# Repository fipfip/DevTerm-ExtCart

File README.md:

# DevTerm-ExtCart

An extension board for the DevTerm, with Commodore64-style 44pin cartridge.

## Design desiderata

Pin assignment:
- Maximum compatibility and function alignment.
- Strong coupling of differential pairs.
- Avoid damage.
All power pins are mirror safe.
Expansion port requirement:
- Pin 21 MUST connect to Pin 23.
- Pin 24 MUST be NC
ROUTE_EN disconnects all routed pins when cartridge is:
- Disconnected
- Inserted the wrong direction
Resource overview:
- 8x internal GPIOs
- 8x external GPIOs
- MIPI-CSI
- 3x USB 2.0
- 1x SPI
- 1x I2C
- 1x UART (Debug)
Resource management pins:
- IO36 for power management
- IO43 for cartridge detection

## PCB Physical specifications

- EXT board:
  - size: 89mm (height) x 101mm (width)
  - thickness: 1mm (source: https://www.ampltd.com/minipcie/)
- Carts:
  - size: 61mm (max height inside DevTerm) x 58.42mm (width)
  - thickness: 1.6mm (source: https://dirtypcbs.com/store/designer/details/12317/1036/cartridge-board-for-commodore-64)

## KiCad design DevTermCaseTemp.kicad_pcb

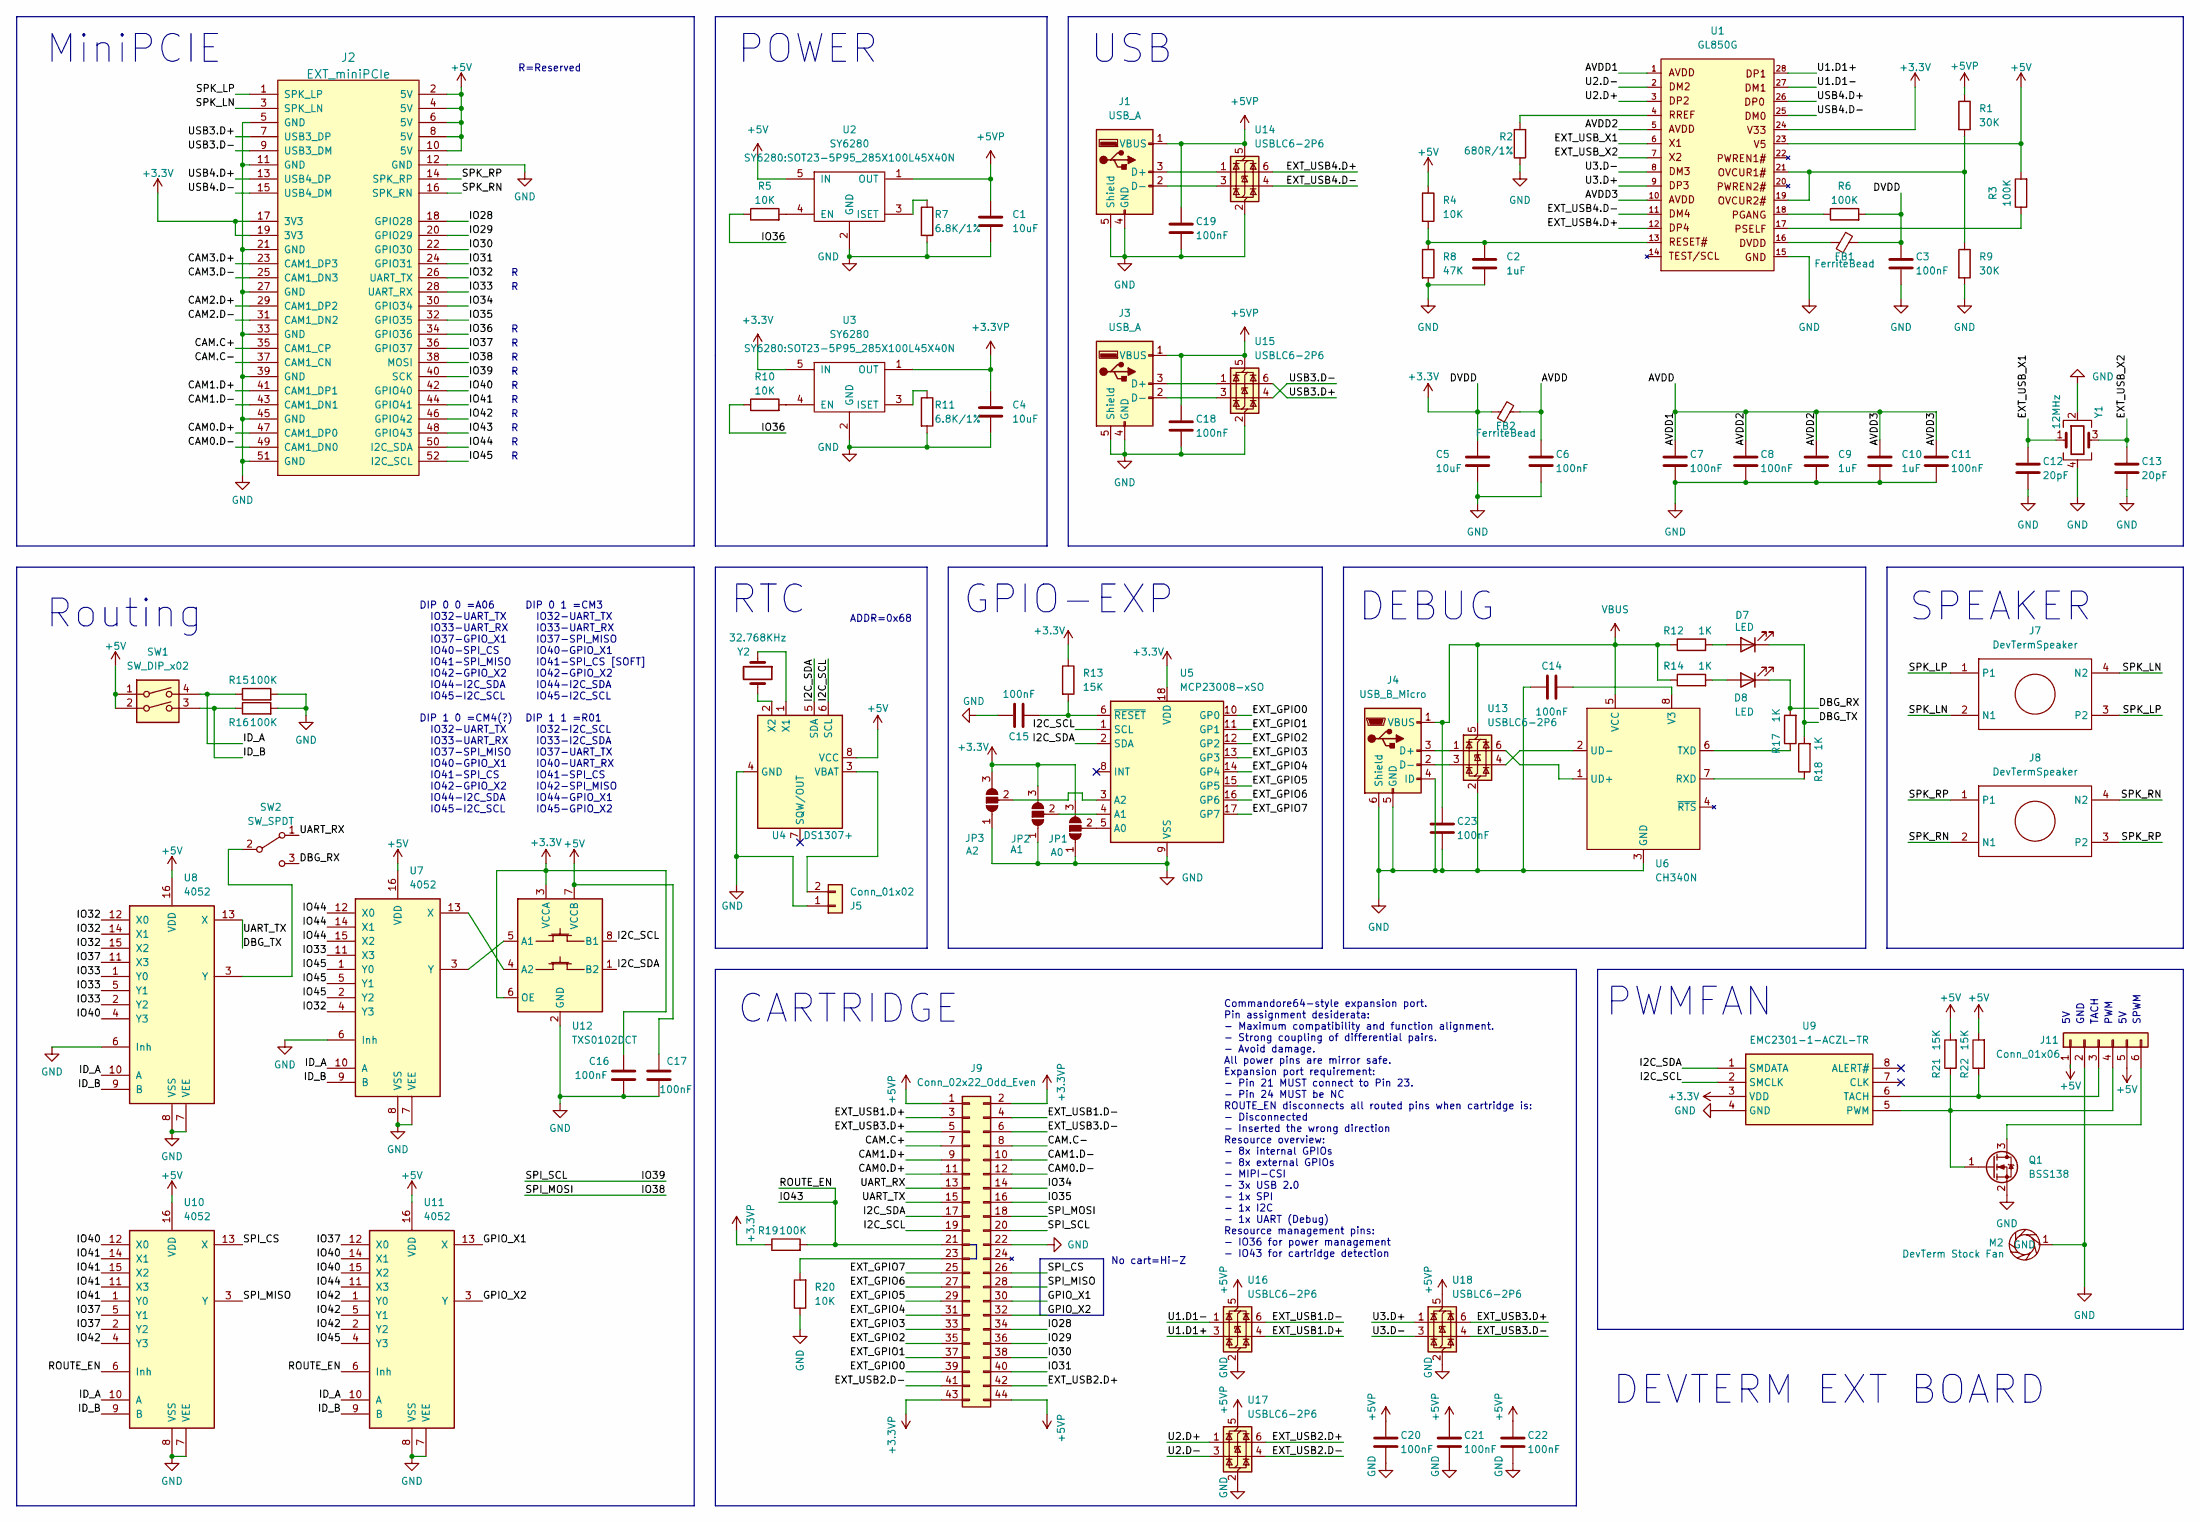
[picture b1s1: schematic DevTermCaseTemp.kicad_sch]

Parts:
C1, C4, C5: 10uF; C_0805_2012Metric
C2, C9, C10: 1uF; C_0805_2012Metric
C3, C6, C7, C8, C11, C14, C15, C16, C17, C18, C19, C20, C21, C22, C23: 100nF; C_0805_2012Metric
C12, C13: 20pF; C_0805_2012Metric
D7, D8: LED; LED_0603_1608Metric
FB1, FB2: FerriteBead; C_0805_2012Metric
J1, J3: USB_A; USB_A_PCBCUT
J2: EXT_miniPCIe; mini-PCIe
J4: USB_B_Micro; USB_Micro-B_Amphenol_10118194_Horizontal
J5: Conn_01x02; Molex_PicoBlade_53048-0210_1x02_P1.25mm_Horizontal
J7, J8: DevTermSpeaker; DevTerm-Speaker
J9: Conn_02x22_Odd_Even; C64-Cart-Socket-Horizontal
J11: Conn_01x06; PinHeader_1x06_P2.00mm_Horizontal
JP1: A0; SolderJumper-3_P1.3mm_Open_Pad1.0x1.5mm
JP2: A1; SolderJumper-3_P1.3mm_Open_Pad1.0x1.5mm
JP3: A2; SolderJumper-3_P1.3mm_Open_Pad1.0x1.5mm
M2: DevTerm Stock Fan; DevTerm-Stock-Fan
Q1: BSS138; SOT-23
R1, R9: 30K; R_0805_2012Metric
R2: 680R/1%; R_0805_2012Metric
R3, R6, R15, R16, R19: 100K; R_0805_2012Metric
R4, R5, R10, R20: 10K; R_0805_2012Metric
R7, R11: 6.8K/1%; R_0805_2012Metric
R8: 47K; R_0805_2012Metric
R12, R14, R17, R18: 1K; R_0805_2012Metric
R13, R21, R22: 15K; R_0805_2012Metric
SW1: SW_DIP_x02; SW_DIP_SPSTx02_Slide_6.7x6.64mm_W8.61mm_P2.54mm_LowProfile
SW2: SW_SPDT; SW_CuK_OS102011MA1QN1_SPDT_Angled
U1: GL850G; SSOP28
U2, U3: SY6280; SOT23-5P95_285X100L45X40N
U4: DS1307+; SOIC-8
U5: MCP23008-xSO; SOIC-18W_7.5x11.6mm_P1.27mm
U6: CH340N; SOP-8_3.9x4.9mm_P1.27mm
U7, U8, U10, U11: 4052; SOIC-16_3.9x9.9mm_P1.27mm
U9: EMC2301-1-ACZL-TR; SOP65P490X110-8N; Mouser Part Number 886-EMC2301-1-ACZLTR
U12: TXS0102DCT; MSOP-8_3x3mm_P0.65mm
U13, U14, U15, U16, U17, U18: USBLC6-2P6; SOT-666
Y1: 12MHz; Crystal_SMD_3225-4Pin_3.2x2.5mm_HandSoldering
Y2: 32.768KHz; Crystal_DS26_D2.0mm_L6.0mm_Horizontal

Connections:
+3.3V: C3.1, C5.1, C16.1, FB1.2, FB2.1, J2.17 (3V3), J2.19 (3V3), JP1.3 (B), JP2.3 (B), JP3.3 (B), R6.2, R13.1, U1.24, U3.5 (IN), U5.18 (VDD), U9.3 (VDD), U12.3 (VCCA), U12.6 (OE)
+3.3VP: C4.1, J9.2, J9.43, R19.1, U3.1 (OUT)
+5V: C17.1, J2.2 (5V), J2.4 (5V), J2.6 (5V), J2.8 (5V), J2.10 (5V), J11.1, J11.5, R3.2, R4.1, R21.2, R22.2, SW1.1, SW1.2, U1.23, U2.5 (IN), U4.8 (VCC), U7.16 (VDD), U8.16 (VDD), U10.16 (VDD), U11.16 (VDD), U12.7 (VCCB)
+5VP: C1.1, C18.1, C19.1, C20.1, C21.1, C22.1, J1.1 (VBUS), J3.1 (VBUS), J9.1, J9.44, R1.1, U2.1 (OUT), U14.5 (VBUS), U15.5 (VBUS), U16.5 (VBUS), U17.5 (VBUS), U18.5 (VBUS)
/AVDD: C6.1, C7.1, C8.1, C9.1, C10.1, C11.1, FB2.2, U1.1, U1.5, U1.10
/CAM0.D+: J2.47 (CAM1_DP0), J9.11
/CAM0.D-: J2.49 (CAM1_DN0), J9.12
/CAM1.D+: J2.41 (CAM1_DP1), J9.9
/CAM1.D-: J2.43 (CAM1_DN1), J9.10
/CAM2.D+: J2.29 (CAM1_DP2)
/CAM2.D-: J2.31 (CAM1_DN2)
/CAM3.D+: J2.23 (CAM1_DP3)
/CAM3.D-: J2.25 (CAM1_DN3)
/CAM.C+: J2.35 (CAM1_CP), J9.7
/CAM.C-: J2.37 (CAM1_CN), J9.8
/DBG_RX: D8.1 (K), R17.2, SW2.3 (C)
/DBG_TX: D7.1 (K), J9.15, R18.2, U8.13 (X)
/EXT_GPIO0: J9.39, U5.10 (GP0)
/EXT_GPIO1: J9.37, U5.11 (GP1)
/EXT_GPIO2: J9.35, U5.12 (GP2)
/EXT_GPIO3: J9.33, U5.13 (GP3)
/EXT_GPIO4: J9.31, U5.14 (GP4)
/EXT_GPIO5: J9.29, U5.15 (GP5)
/EXT_GPIO6: J9.27, U5.16 (GP6)
/EXT_GPIO7: J9.25, U5.17 (GP7)
/EXT_USB1.D+: J9.3, U16.4 (I/O2)
/EXT_USB1.D-: J9.4, U16.6 (I/O1)
/EXT_USB2.D+: J9.42, U17.6 (I/O1)
/EXT_USB2.D-: J9.41, U17.4 (I/O2)
/EXT_USB3.D+: J9.5, U18.6 (I/O1)
/EXT_USB3.D-: J9.6, U18.4 (I/O2)
/EXT_USB4.D+: U1.12, U14.6 (I/O1)
/EXT_USB4.D-: U1.11, U14.4 (I/O2)
/EXT_USB_X1: C12.1, U1.6, Y1.1
/EXT_USB_X2: C13.1, U1.7, Y1.3
/GPIO_X1: J9.30, U11.13 (X)
/GPIO_X2: J9.32, U11.3 (Y)
/I2C_SCL: J9.19, U4.6 (SCL), U5.1 (SCL), U9.2 (SMCLK), U12.8 (B1)
/I2C_SDA: J9.17, U4.5 (SDA), U5.2 (SDA), U9.1 (SMDATA), U12.1 (B2)
/ID_A: R15.1, SW1.4, U7.10 (A), U8.10 (A), U10.10 (A), U11.10 (A)
/ID_B: R16.1, SW1.3, U7.9 (B), U8.9 (B), U10.9 (B), U11.9 (B)
/IO28: J2.18 (GPIO28), J9.34
/IO29: J2.20 (GPIO29), J9.36
/IO30: J2.22 (GPIO30), J9.38
/IO31: J2.24 (GPIO31), J9.40
/IO32: J2.26 (UART_TX), U7.4 (Y3), U8.12 (X0), U8.14 (X1), U8.15 (X2)
/IO33: J2.28 (UART_RX), U7.11 (X3), U8.1 (Y0), U8.2 (Y2), U8.5 (Y1)
/IO34: J2.30 (GPIO34), J9.14
/IO35: J2.32 (GPIO35), J9.16
/IO36: J2.34 (GPIO36), R5.1, R10.1
/IO37: J2.36 (GPIO37), U8.11 (X3), U10.2 (Y2), U10.5 (Y1), U11.12 (X0)
/IO38: J2.38 (MOSI), J9.18
/IO39: J2.40 (SCK), J9.20
/IO40: J2.42 (GPIO40), U8.4 (Y3), U10.12 (X0), U11.14 (X1), U11.15 (X2)
/IO41: J2.44 (GPIO41), U10.1 (Y0), U10.11 (X3), U10.14 (X1), U10.15 (X2)
/IO42: J2.46 (GPIO42), U10.4 (Y3), U11.1 (Y0), U11.2 (Y2), U11.5 (Y1)
/IO43: J2.48 (GPIO43), J9.21, R19.2, U10.6 (Inh), U11.6 (Inh)
/IO44: J2.50 (I2C_SDA), U7.12 (X0), U7.14 (X1), U7.15 (X2), U11.11 (X3)
/IO45: J2.52 (I2C_SCL), U7.1 (Y0), U7.2 (Y2), U7.5 (Y1), U11.4 (Y3)
/SPI_CS: J9.26, U10.13 (X)
/SPI_MISO: J9.28, U10.3 (Y)
/SPK_LN: J2.3 (SPK_LN), J7.2 (N1), J7.4 (N2)
/SPK_LP: J2.1 (SPK_LP), J7.1, J7.3 (P2)
/SPK_RN: J2.16 (SPK_RN), J8.2 (N1), J8.4 (N2)
/SPK_RP: J2.14 (SPK_RP), J8.1, J8.3 (P2)
/U1.D1+: U1.28, U16.3 (I/O2)
/U1.D1-: U1.27, U16.1 (I/O1)
/U2.D+: U1.3, U17.1 (I/O1)
/U2.D-: U1.2, U17.3 (I/O2)
/U3.D+: U1.9, U18.1 (I/O1)
/U3.D-: U1.8, U18.3 (I/O2)
/UART_RX: J9.13, SW2.1 (A)
/USB3.D+: J2.7 (USB3_DP), U15.6 (I/O1)
/USB3.D-: J2.9 (USB3_DM), U15.4 (I/O2)
/USB4.D+: J2.13 (USB4_DP), U1.26
/USB4.D-: J2.15 (USB4_DM), U1.25
GND: C1.2, C2.2, C3.2, C4.2, C5.2, C6.2, C7.2, C8.2, C9.2, C10.2, C11.2, C12.2, C13.2, C14.2, C15.1, C16.2, C17.2, C18.2, C19.2, C20.2, C21.2, C22.2, C23.2, J1.4 (GND), J1.5 (Shield), J2.5 (GND), J2.11 (GND), J2.12 (GND), J2.21 (GND), J2.27 (GND), J2.33 (GND), J2.39 (GND), J2.45 (GND), J2.51 (GND), J3.4 (GND), J3.5 (Shield), J4.4 (ID), J4.5 (GND), J4.6 (Shield), J5.1, J9.22, J11.2, JP1.1 (A), JP2.1 (A), JP3.1 (A), M2.1 (GND), Q1.2 (S), R2.1, R7.2, R8.2, R9.2, R11.2, R15.2, R16.2, R20.1, U1.15, U2.2 (GND), U3.2 (GND), U4.4 (GND), U5.9 (VSS), U6.3 (GND), U7.6 (Inh), U7.7 (VEE), U7.8 (VSS), U8.6 (Inh), U8.7 (VEE), U8.8 (VSS), U9.4 (GND), U10.7 (VEE), U10.8 (VSS), U11.7 (VEE), U11.8 (VSS), U12.2 (GND), U13.2 (GND), U14.2 (GND), U15.2 (GND), U16.2 (GND), U17.2 (GND), U18.2 (GND), Y1.2, Y1.4
unnamed: C2.1, R4.2, R8.1, U1.13
unnamed: D7.2 (A), R12.2
unnamed: D8.2 (A), R14.2
unnamed: FB1.1, U1.16
unnamed: J1.3 (D+), U14.1 (I/O1)
unnamed: J1.2 (D-), U14.3 (I/O2)
unnamed: J3.3 (D+), U15.1 (I/O1)
unnamed: J3.2 (D-), U15.3 (I/O2)
unnamed: J4.3 (D+), U13.1 (I/O1)
unnamed: J4.2 (D-), U13.3 (I/O2)
unnamed: J5.2, U4.3 (VBAT)
unnamed: J9.23, R20.2
unnamed: J11.3, R22.1, U9.6 (TACH)
unnamed: J11.4, Q1.1 (G), R21.1, U9.5 (PWM)
unnamed: J11.6, Q1.3 (D)
unnamed: JP1.2 (C), U5.5 (A0)
unnamed: JP2.2 (C), U5.4 (A1)
unnamed: JP3.2 (C), U5.3 (A2)
unnamed: R1.2, R9.1, U1.19, U1.21
unnamed: R2.2, U1.4
unnamed: R3.1, U1.17
unnamed: R6.1, U1.18
unnamed: SW2.2 (B), U8.3 (Y)
unnamed: R5.2, U2.4 (EN)
unnamed: R7.1, U2.3 (ISET)
unnamed: R10.2, U3.4 (EN)
unnamed: R11.1, U3.3 (ISET)
unnamed: U4.1 (X1), Y2.1
unnamed: U4.2 (X2), Y2.2
unnamed: C15.2, R13.2, U5.6 (~RESET)
unnamed: R18.1, U6.7 (RXD)
unnamed: R17.1, U6.6 (TXD)
unnamed: U6.1 (UD+), U13.6 (I/O1)
unnamed: U6.2 (UD-), U13.4 (I/O2)
unnamed: C14.1, U6.8 (V3)
unnamed: U7.3 (Y), U12.5 (A1)
unnamed: U7.13 (X), U12.4 (A2)
VBUS: C23.1, J4.1 (VBUS), R12.1, R14.1, U6.5 (VCC), U13.5 (VBUS)

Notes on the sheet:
CARTRIDGE
Commandore64-style expansion port. Pin assignment desiderata: - Maximum compatibility and function alignment. - Strong coupling of differential pairs. - Avoid damage. All power pins are mirror safe. Expansion port requirement: - Pin 21 MUST connect to Pin 23. - Pin 24 MUST be NC ROUTE_EN disconnect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
DIP 0 0 =A06 IO32-UART_TX IO33-UART_RX IO37-GPIO_X1 IO40-SPI_CS IO41-SPI_MISO IO42-GPIO_X2 IO44-I2C_SDA IO45-I2C_SCL
GPIO-EXP
MiniPCIE
USB
R=Reserved
DIP 0 1 =CM3 IO32-UART_TX IO33-UART_RX IO37-SPI_MISO IO40-GPIO_X1 IO41-SPI_CS [SOFT] IO42-GPIO_X2 IO44-I2C_SDA IO45-I2C_SCL
DEVTERM EXT BOARD
GND
POWER
ADDR=0x68
TACH
PWMFAN
DEBUG
PWM
Routing
SPWM
SPEAKER
No cart=Hi-Z
DIP 1 1 =R01 IO32-I2C_SCL IO33-I2C_SDA IO37-UART_TX IO40-UART_RX IO41-SPI_CS IO42-SPI_MISO IO44-GPIO_X1 IO45-GPIO_X2
DIP 1 0 =CM4(?) IO32-UART_TX IO33-UART_RX IO37-SPI_MISO IO40-GPIO_X1 IO41-SPI_CS IO42-GPIO_X2 IO44-I2C_SDA IO45-I2C_SCL
RTC

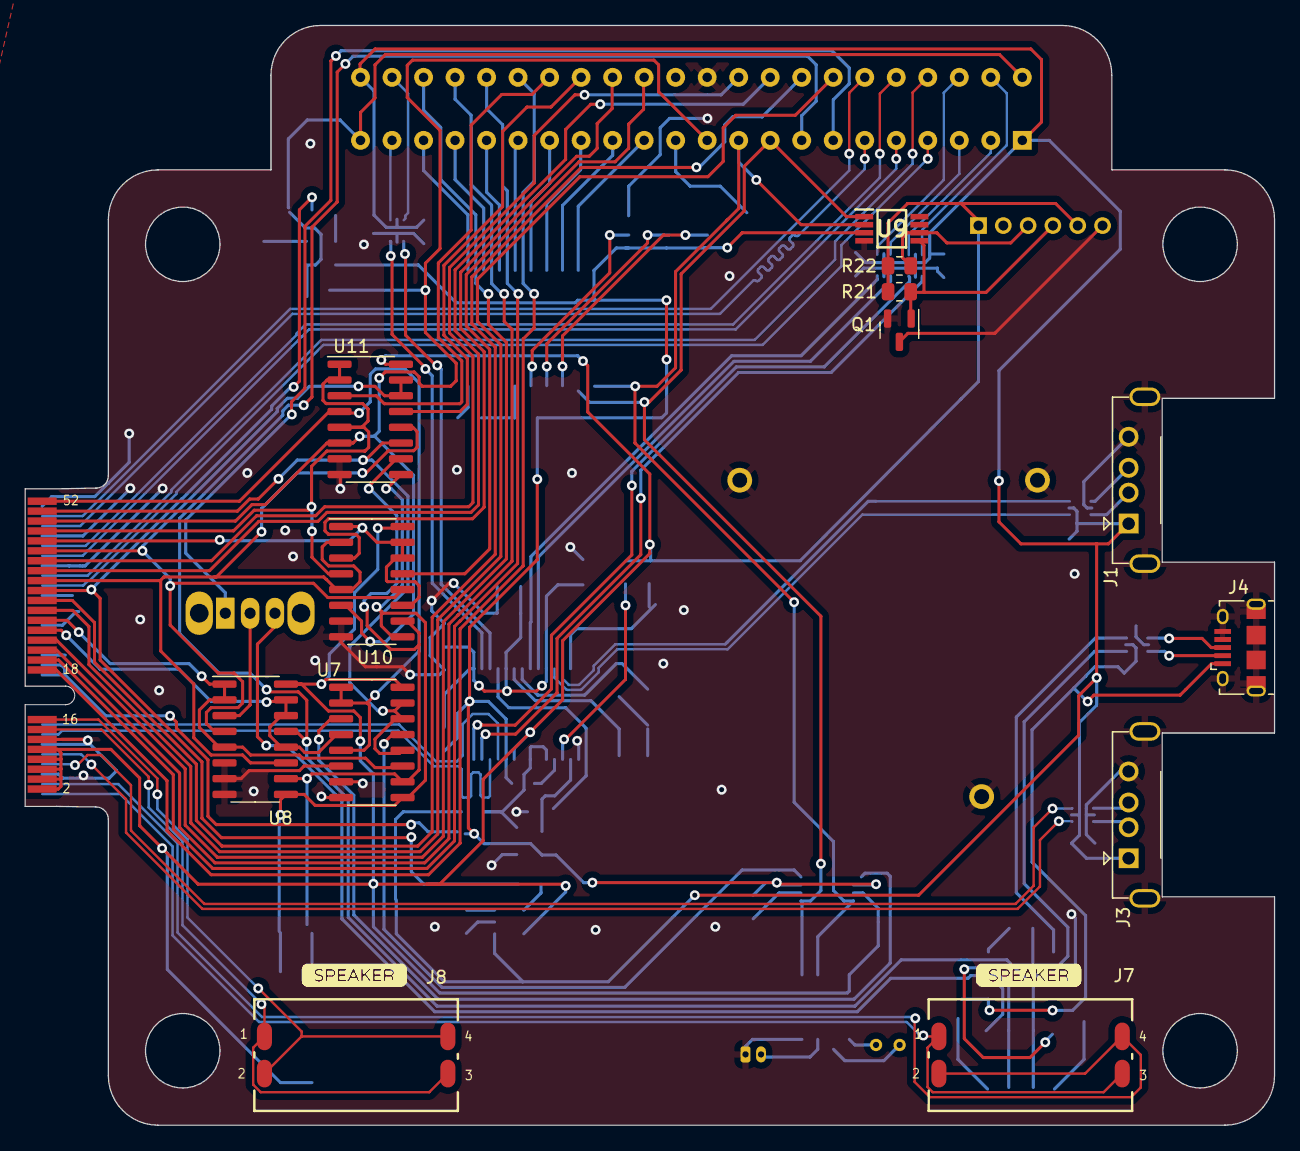
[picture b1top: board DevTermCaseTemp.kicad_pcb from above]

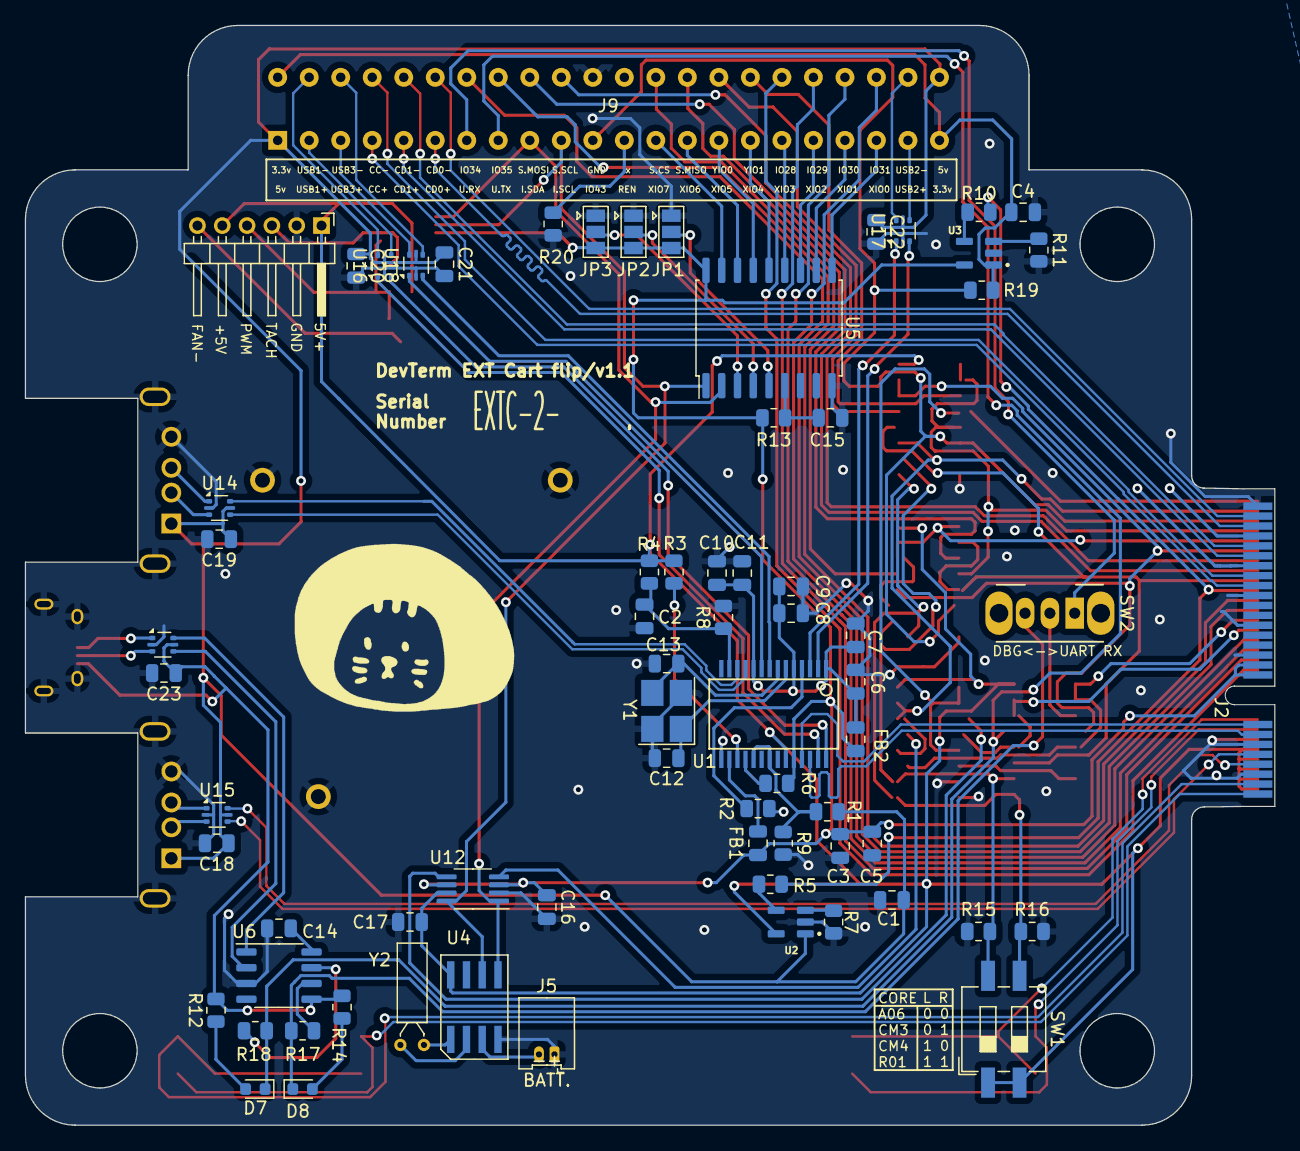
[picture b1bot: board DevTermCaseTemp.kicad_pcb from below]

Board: 2 copper layers, 100.7 x 88.6 mm, 85 parts (72 on the bottom side), 111 nets.

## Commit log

2023-01-16 in production. good luck!
2023-01-23 i2c level shifter to ssop
2023-02-07 v3 is finalized
2023-02-07 done v4 routing
2023-02-08 add uart rx switch
2023-02-17 turbo fan is now a component
2023-02-17 cleanup
2023-02-17 add BOM table
2023-02-17 add ROUTE_EN pull down resistor
2023-02-28 add printer cart submodule
2023-03-28 drop submodules, hard to update
2023-04-01 Add R20 to BOM
2023-04-05 update B.Silkscreen to annotate RTC batt and DBG/UART RX switch
2023-04-05 after adding R20, Pin 23 is not GND any more. Annotate as REN.
2023-08-14 File cleanup
    Moved library files into /lib/ directory, moved media in /media/ folder
2024-07-10 Schematic: - Replace GP7101 with EMC2301 and add support for directly driven fan - Replace 3505/3507 fan with either a CUI Devices CBM-35CF or stock DevTerm fan - Use correct footprint for MCP23008
    Board:
    - Overhaul MIPI CSI line to match impedance and enhance EMC
    - Route new fan component
2024-07-10 Fix supply of EMC2301, add serial number field
2024-07-10 Final error correction and DRC
    - fixed minor silkscreen mistakes
    - added 3D models of fan and C64 connector
    - Updated README.md
2024-11-06 Replaced ESD surge diodes with USBLC6
2024-11-07 Added bypass caps for USB ESD surge protection as specified in datasheet.
    + Updated silkscreen for version and serial number
